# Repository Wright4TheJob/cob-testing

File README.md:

# cob-testing
Software for evaluation of cob blocks being tested at The University of Tulsa.
The data logging program monitors ambient temperature and humidity and internal moisture for up to 8 direct moisture resistance sensors. Data is taken at regular intervals and written at each interval to a text file for insurance against power outage. 

The system is built on a raspberry pi, currently running on a Pi 2 model B.

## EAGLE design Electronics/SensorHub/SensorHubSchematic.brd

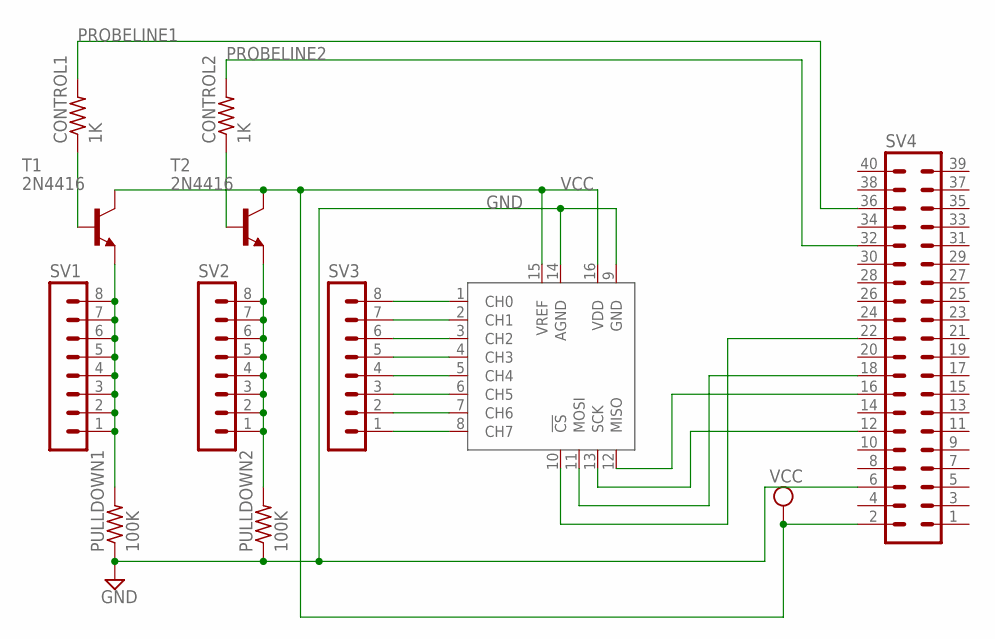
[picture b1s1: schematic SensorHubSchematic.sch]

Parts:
CONTROL1, CONTROL2: 1K; 0207/10
PULLDOWN1, PULLDOWN2: 100K; 0207/10
SV1, SV2, SV3: MA08-1
SV4: MA20-2
T1, T2: 2N4416; TO92
U$1: MCP3008P; DIL16

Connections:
GND: PULLDOWN1.1, PULLDOWN2.1, SV4.6, U$1.9 (GND), U$1.14 (AGND)
unnamed: PULLDOWN1.2, SV1.1, SV1.2, SV1.3, SV1.4, SV1.5, SV1.6, SV1.7, SV1.8, T1.3 (E)
unnamed: PULLDOWN2.2, SV2.1, SV2.2, SV2.3, SV2.4, SV2.5, SV2.6, SV2.7, SV2.8, T2.3 (E)
unnamed: SV3.1, U$1.8 (CH7)
unnamed: SV3.2, U$1.7 (CH6)
unnamed: SV3.3, U$1.6 (CH5)
unnamed: SV3.4, U$1.5 (CH4)
unnamed: SV3.5, U$1.4 (CH3)
unnamed: SV3.6, U$1.3 (CH2)
unnamed: SV3.7, U$1.2 (CH1)
unnamed: SV3.8, U$1.1 (CH0)
unnamed: CONTROL1.1, T1.2 (B)
unnamed: CONTROL2.1, T2.2 (B)
unnamed: SV4.18, U$1.11 (MOSI)
unnamed: SV4.22, U$1.10 (!CS)
unnamed: SV4.12, U$1.13 (SCK)
unnamed: SV4.16, U$1.12 (MISO)
PROBELINE1: CONTROL1.2, SV4.36
PROBELINE2: CONTROL2.2, SV4.32
VCC: SV4.2, T1.1 (C), T2.1 (C), U$1.15 (VREF), U$1.16 (VDD)

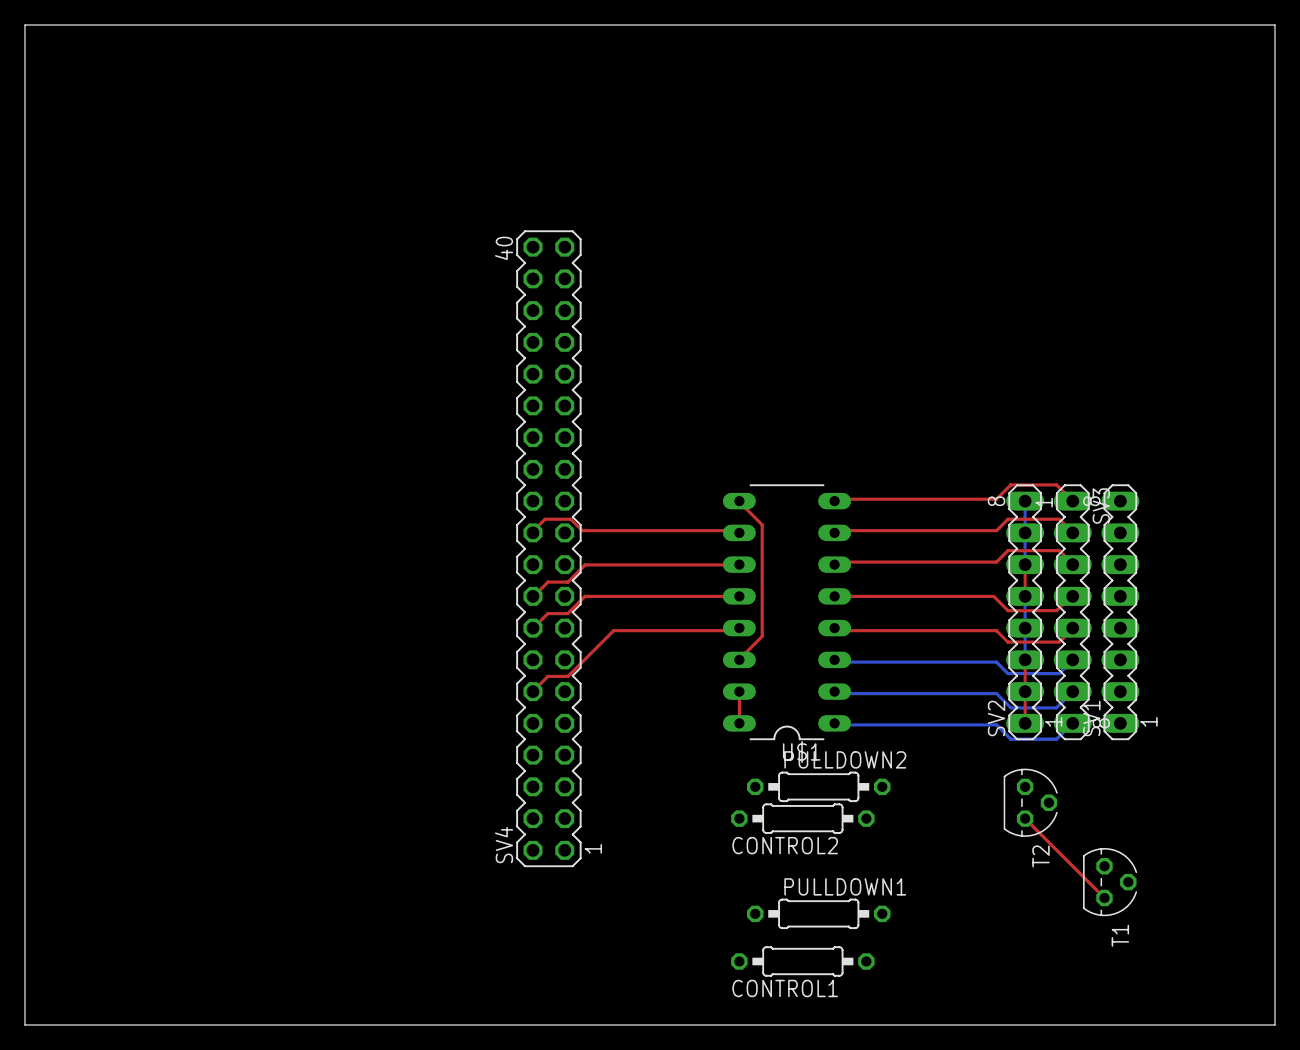
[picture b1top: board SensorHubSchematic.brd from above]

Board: 2 copper layers, 100.0 x 80.0 mm, 11 parts (0 on the bottom side), 20 nets.

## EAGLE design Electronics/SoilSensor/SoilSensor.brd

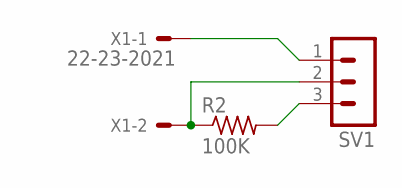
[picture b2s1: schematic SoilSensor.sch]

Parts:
R2: 100K; 0411/15
SV1: MA03-1
X1: 22-23-2021

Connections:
unnamed: SV1.1, X1.1
unnamed: R2.1, SV1.2, X1.2
unnamed: R2.2, SV1.3

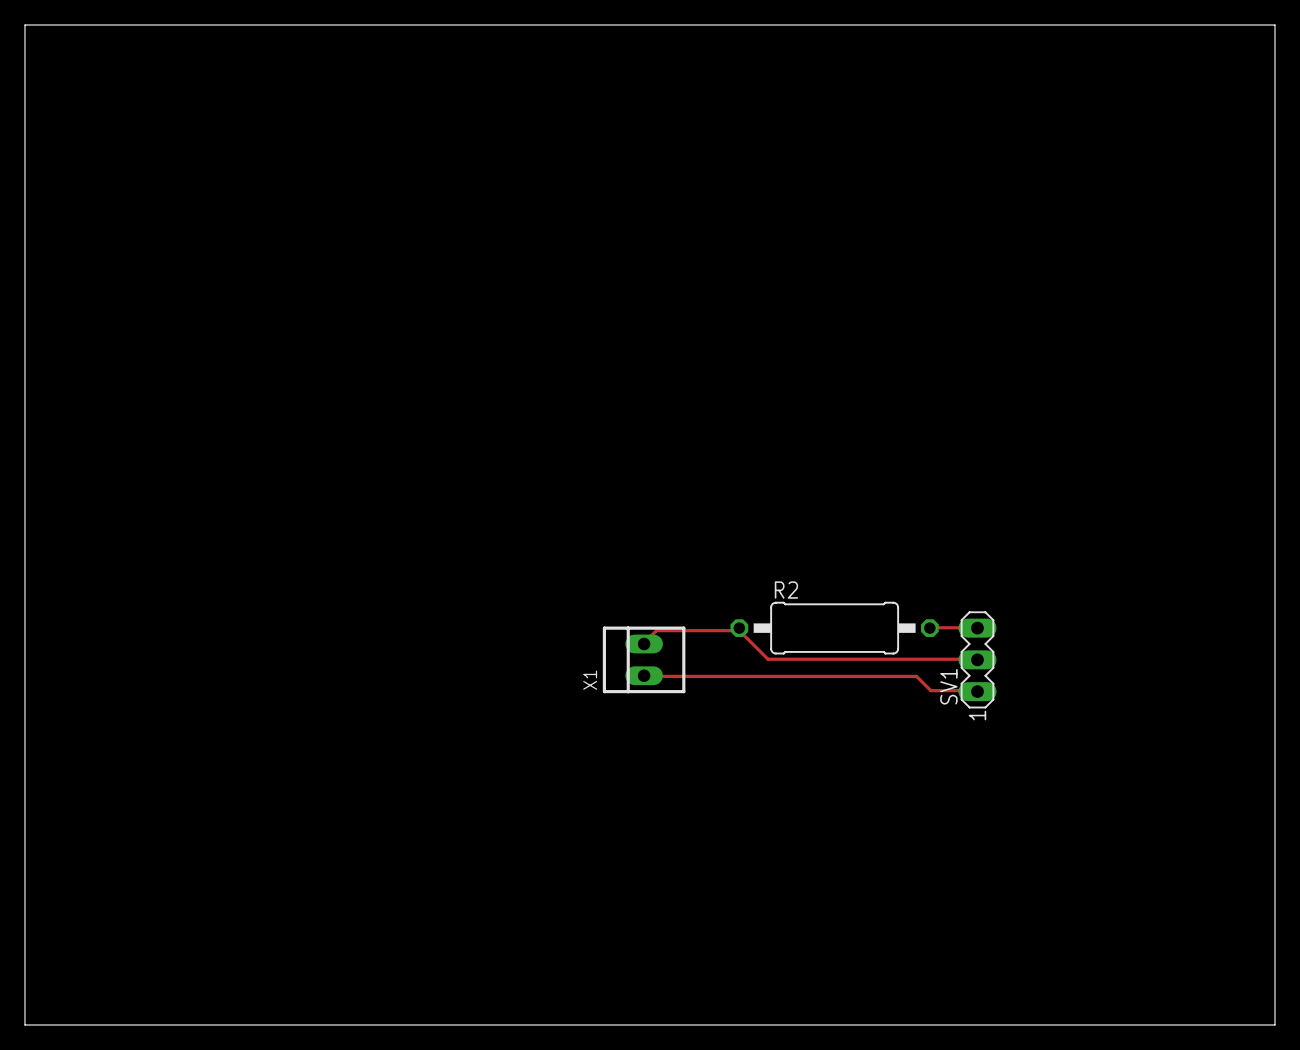
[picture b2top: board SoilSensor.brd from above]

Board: 2 copper layers, 100.0 x 80.0 mm, 3 parts (0 on the bottom side), 3 nets.

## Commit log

2017-01-05 Initializing the ToDo file to keep a running list of things to add
2017-01-05 Added some items to do
2017-01-05 Modified todo list
2017-01-05 Added items to do
2017-01-06 Added primary python script to git repo
2017-01-06 Split program into two files, including one module for general use. Generalized delays before reading data
2017-01-07 Got delays working properly. Ambient sensor timing out without being plugged in. Test with sensor later
2017-02-13 Electronics documentation added
